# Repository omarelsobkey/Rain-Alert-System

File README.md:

#  Rain Alert System (PCB Project)

## Features 

- when rain falls there is a sound alert using buzzer connected to timer555 in Astable mode
- when rain falls there is a visual alert using LED connected to transistor

## Source
https://www.electronicshub.org/rain-alarm-project/

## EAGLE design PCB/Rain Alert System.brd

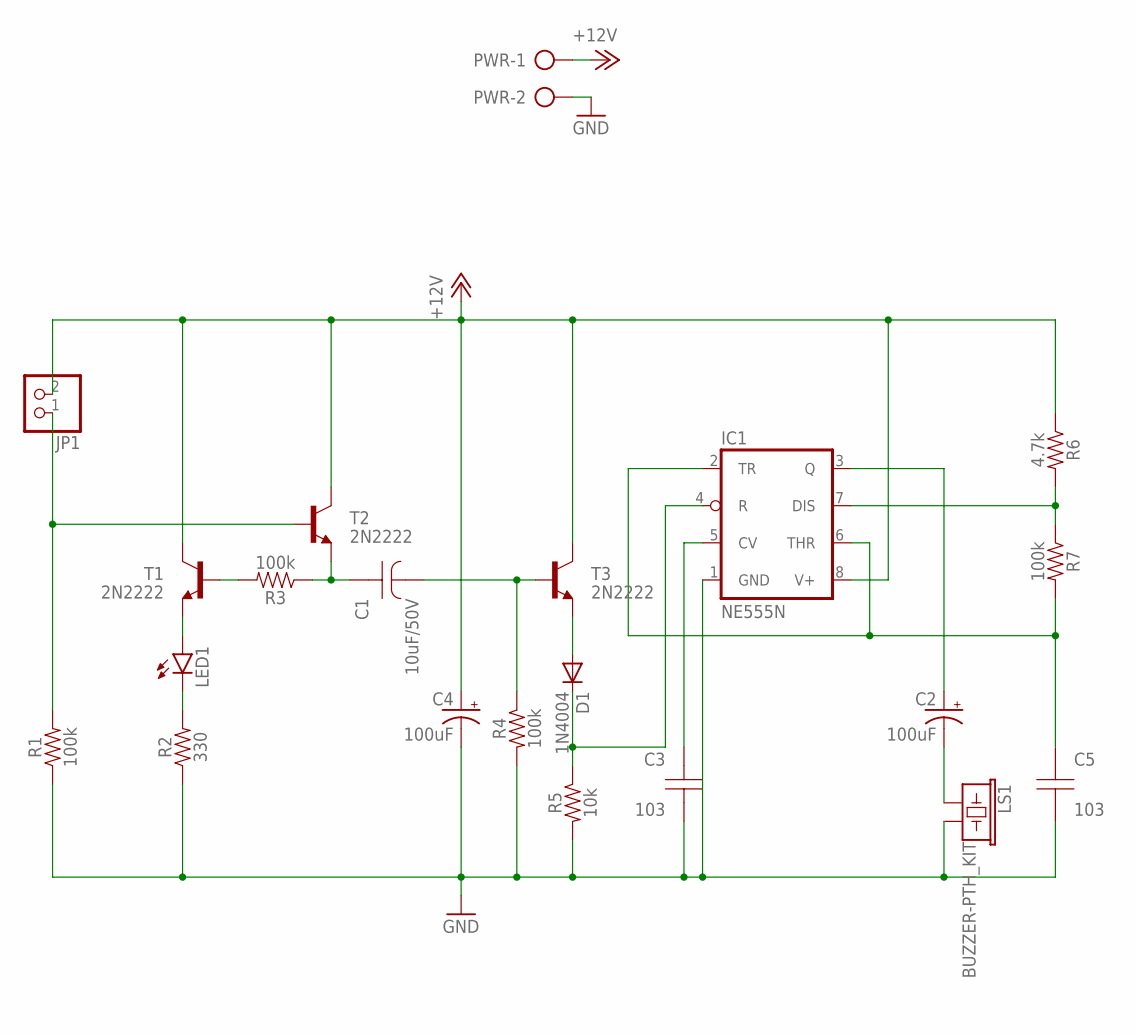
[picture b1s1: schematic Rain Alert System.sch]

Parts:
C1: 10uF/50V; D5
C2, C4: 100uF; CPOL-RADIAL-2.5MM-6.5MM
C3, C5: 103; P2.8
D1: 1N4004; DO41-10
IC1: NE555N; DIL08-ROUND
JP1: PINHD-1X2/90; 1X02/90
LED1: LED5MM
LS1: BUZZER-PTH_KIT; BUZZER-12MM-KIT
PWR: 2P
R1, R3, R4, R7: 100k; AXIAL-0.3
R2: 330; AXIAL-0.3
R5: 10k; AXIAL-0.3
R6: 4.7k; AXIAL-0.3
T1, T2, T3: 2N2222; TO92-EBC-OVAL

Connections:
+12V: C4.1 (+), IC1.8 (V+), JP1.2, PWR.1, R6.P$1 (1), T1.C, T2.C, T3.C
GND: C3.2 (K1), C4.2 (-), C5.2 (K1), IC1.1 (GND), LS1.- (2), PWR.2, R1.P$1 (1), R2.P$1 (1), R4.P$2 (2), R5.P$2 (2)
unnamed: LED1.K (C), R2.P$2 (2)
unnamed: JP1.1, R1.P$2 (2), T2.B
unnamed: LED1.A, T1.E
unnamed: R3.P$2 (2), T1.B
unnamed: C1.A, R3.P$1 (1), T2.E
unnamed: C1.K, R4.P$1 (1), T3.B
unnamed: D1.C, IC1.4 (R), R5.P$1 (1)
unnamed: D1.A, T3.E
unnamed: C2.2 (-), LS1.+ (1)
unnamed: C2.1 (+), IC1.3 (Q)
unnamed: C3.1 (A1), IC1.5 (CV)
unnamed: IC1.7 (DIS), R6.P$2 (2), R7.P$1 (1)
unnamed: C5.1 (A1), IC1.2 (TR), IC1.6 (THR), R7.P$2 (2)

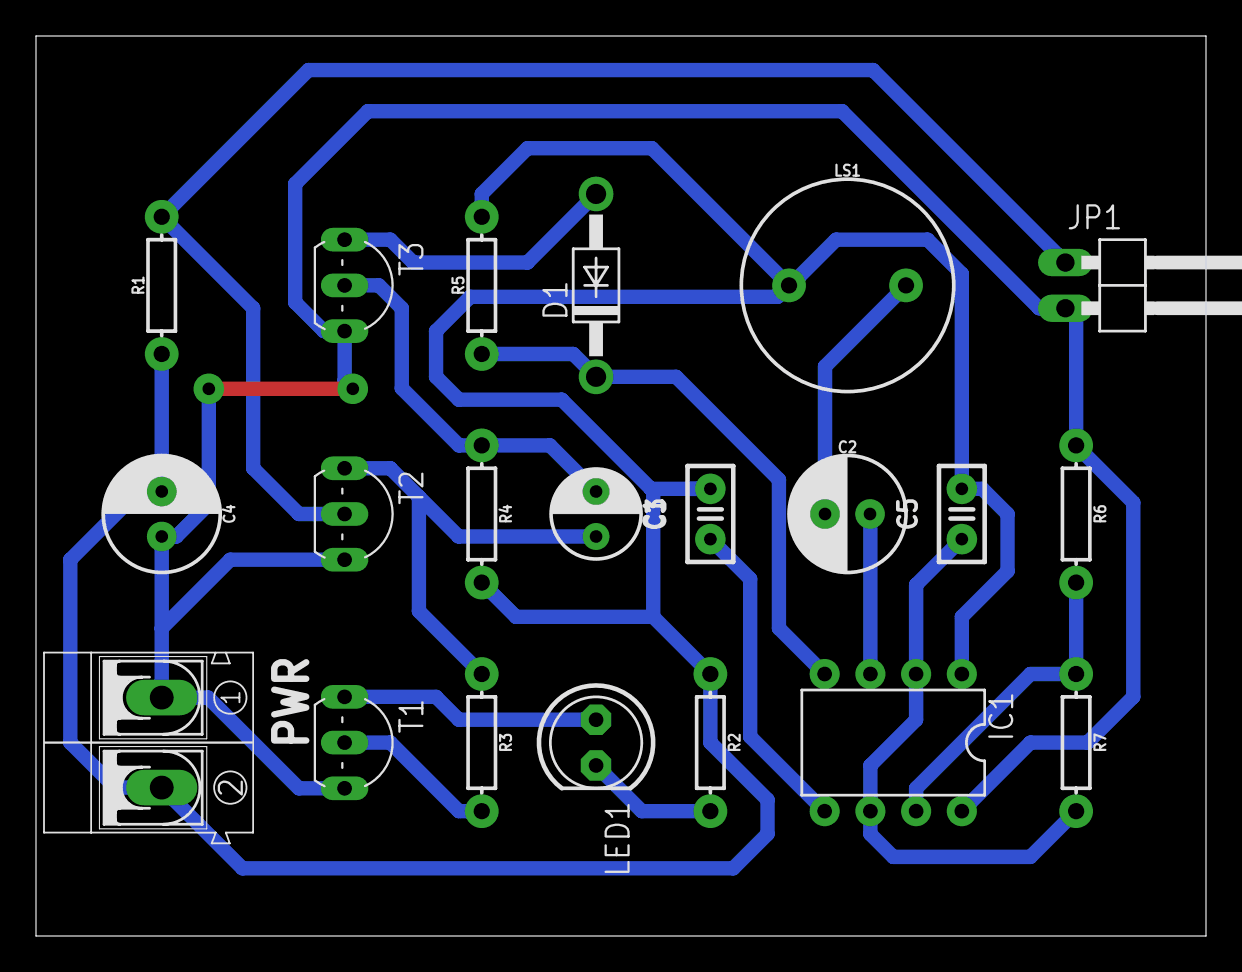
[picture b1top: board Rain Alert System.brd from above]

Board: 2 copper layers, 65.0 x 50.0 mm, 21 parts (0 on the bottom side), 15 nets.

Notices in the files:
parts and their libraries:
SparkFun-Electromechanical: Licensing: Creative Commons ShareAlike 4.0 International - https://creativecommons.org/licenses/by-sa/4.0
